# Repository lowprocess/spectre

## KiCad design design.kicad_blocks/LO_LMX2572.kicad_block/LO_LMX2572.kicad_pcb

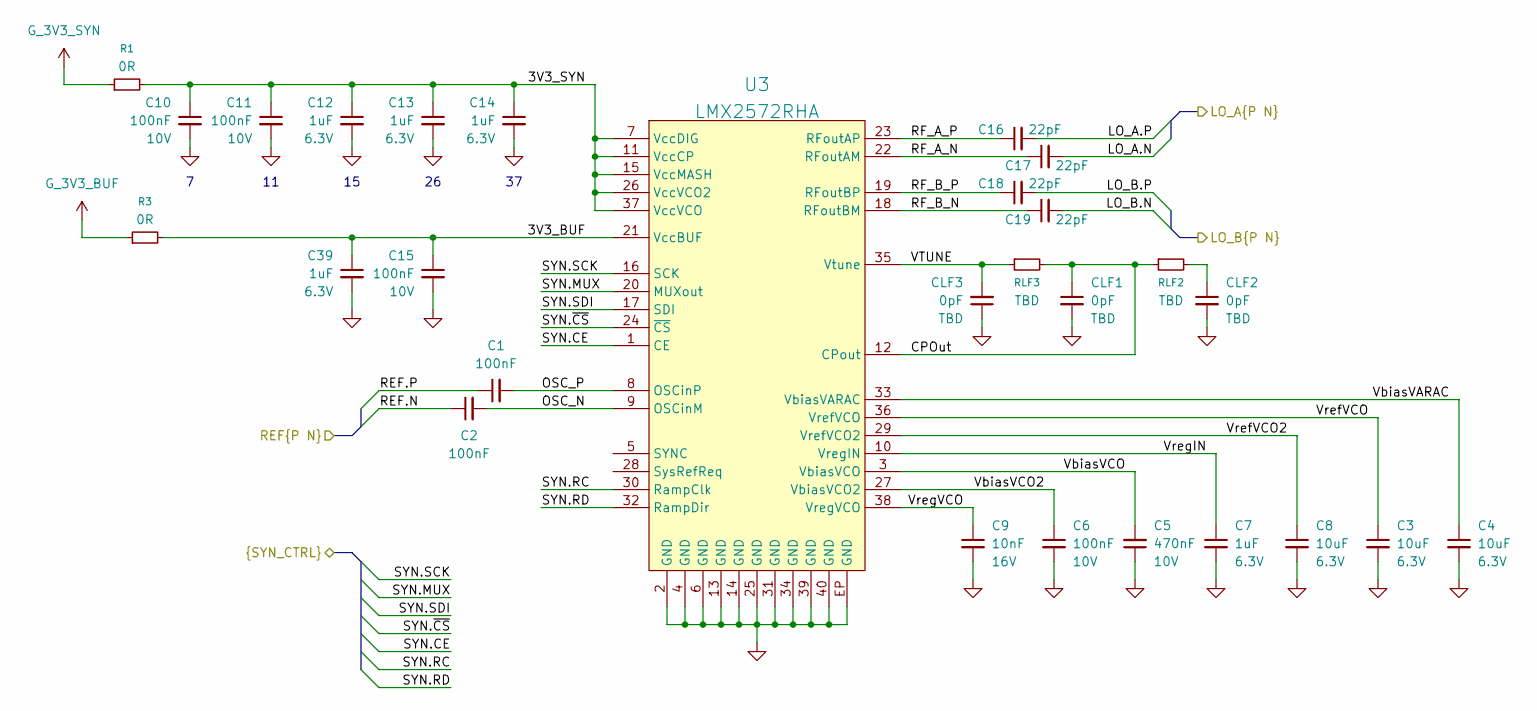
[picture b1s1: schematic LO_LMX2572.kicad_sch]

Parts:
C1, C2, C6, C10, C11, C15: 100nF; C_0402; Tolerance 10%; Voltage 10V; PartNumber GRM155R71A104K
C3, C4, C8: 10uF; C_0402; Tolerance 20%; Voltage 6.3V; PartNumber GRM155R60J106M
C5: 470nF; C_0402; Tolerance 10%; Voltage 10V; PartNumber GRM155R71A474K
C7, C12, C13, C14, C39: 1uF; C_0402; Tolerance 10%; Voltage 6.3V; PartNumber GRM155R70J105K
C9: 10nF; C_0402; Tolerance 10%; Voltage 16V; PartNumber GRM155R71C103K
C16, C17, C18, C19: 22pF; C_0201; Tolerance 5%; Voltage 25V; PartNumber GRM0335C1E220J
CLF1: 0pF; C_0603; Tolerance TBD; Voltage TBD; PartNumber 0603_TBD
CLF2, CLF3: 0pF; C_0402; Tolerance TBD; Voltage TBD; PartNumber 0402_TBD
R1, R3: 0R; R_0402; Tolerance 0%; PartNumber CRCW04020000Z0ED
RLF2, RLF3: TBD; R_0402; Tolerance TBD; PartNumber 0402_TBD
U3: QFN40; PartNumber LMX2572RHA

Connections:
/LO1/3V3_BUF: C15.1, C39.1, R3.2, U3.21 (VccBUF)
/LO1/3V3_SYN: C10.1, C11.1, C12.1, C13.1, C14.1, R1.2, U3.7 (VccDIG), U3.11 (VccCP), U3.15 (VccMASH), U3.26 (VccVCO2), U3.37 (VccVCO)
/LO1/CPOut: CLF1.1, RLF2.1, RLF3.2, U3.12 (CPout)
/LO1/LO_A.N: C17.2
/LO1/LO_A.P: C16.2
/LO1/LO_B.N: C19.2
/LO1/LO_B.P: C18.2
/LO1/OSC_N: C2.2, U3.9 (OSCinM)
/LO1/OSC_P: C1.2, U3.8 (OSCinP)
/LO1/REF.N: C2.1
/LO1/REF.P: C1.1
/LO1/RF_A_N: C17.1, U3.22 (RFoutAM)
/LO1/RF_A_P: C16.1, U3.23 (RFoutAP)
/LO1/RF_B_N: C19.1, U3.18 (RFoutBM)
/LO1/RF_B_P: C18.1, U3.19 (RFoutBP)
/LO1/SYN.CE: U3.1 (CE)
/LO1/SYN.MUX: U3.20 (MUXout)
/LO1/SYN.RC: U3.30 (RampClk)
/LO1/SYN.RD: U3.32 (RampDir)
/LO1/SYN.SCK: U3.16 (SCK)
/LO1/SYN.SDI: U3.17 (SDI)
/LO1/SYN.~CS: U3.24 (~CS)
/LO1/VTUNE: CLF3.2, RLF3.1, U3.35 (Vtune)
/LO1/VbiasVARAC: C4.1, U3.33 (VbiasVARAC)
/LO1/VbiasVCO: C5.2, U3.3 (VbiasVCO)
/LO1/VbiasVCO2: C6.1, U3.27 (VbiasVCO2)
/LO1/VrefVCO: C3.1, U3.36 (VrefVCO)
/LO1/VrefVCO2: C8.1, U3.29 (VrefVCO2)
/LO1/VregIN: C7.1, U3.10 (VregIN)
/LO1/VregVCO: C9.1, U3.38 (VregVCO)
GND: C3.2, C4.2, C5.1, C6.2, C7.2, C8.2, C9.2, C10.2, C11.2, C12.2, C13.2, C14.2, C15.2, C39.2, CLF1.2, CLF2.2, CLF3.1, U3.2 (GND), U3.4 (GND), U3.6 (GND), U3.13 (GND), U3.14 (GND), U3.25 (GND), U3.31 (GND), U3.34 (GND), U3.39 (GND), U3.40 (GND), U3.EP (GND)
G_3V3_BUF: R3.1
G_3V3_SYN: R1.1
unnamed: CLF2.1, RLF2.2

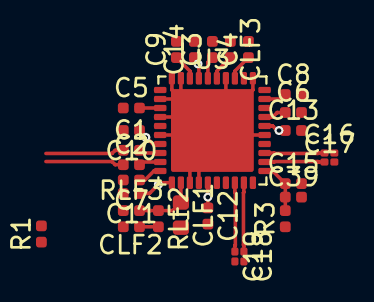
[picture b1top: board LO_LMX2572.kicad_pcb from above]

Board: 2 copper layers, 28 parts (0 on the bottom side), 19 nets.
